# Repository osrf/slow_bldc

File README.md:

# slow_bldc

## parts selection

### microcontrollers
Goal: Fast Cortex-M with FPU (at least for now). HS USB would be nice for tons of datalogging, but not necessarily required.
  * Selection: STM32F303CCT
  * Other parts considered:
    * STM32F723ZET6: a bit spendy but is fast with HS USB, which is neat.
    * STM32F4
      * Access line: F401, F410, F411, F412, F413 only have one ADC
      * Fancier ones have multiple ADC's which would be nicer.
    * Atmel SAM E / V / S

### motor driver
Goal: something completely-integrated with power capacity comfortable for 1A to 2A.
  * Selection: [TI DRV8312](http://www.ti.com/product/DRV8312)

### encoder
Requirements: SPI interface, relatively high resolution
  * Selection: AMS 5048A
    * 14 bit, SPI, 3.3v single-supply, 11 kHz
  * Other parts considered:
    * AMS AS5047D and AS5047P are intended for high-speed BLDC and automatically compensate for encoder latency
      * super cool, but probably not necessary for super low-speed applications
    * Melexis MLX90316
      * 12 bit, SPI
      * 5V supply
      * 1 kHz
    * MPS MA700
      * 3v3 supply, only 7 mA
      * 11 bit
      * 500 kHz
      * can be mounted off-axis and calibrated for donut magnets
    * Allegro A1335
      * 12 bit, SPI
      * can be mounted off-axis
    * AK7451
      * 12 bit
  * Analog output IC's are pretty difference since they output analog sine/cosine, which allows lots of flexibility would would require high-precision simultaneous-sampling ADC to be awesome
    * NXP KMZ60
    * KMT37
    * NVE AAT00x is super low power and tiny since it just provides the sine/cosine half bridges; you need to supply amps and ADC's
    * AS5115 has differential analog sine/cosine outputs

### comms
  * MCU has USB full-speed (12 mbps)
  * Half-duplex RS-485 IC included for chaining these boards together: SN65HVD75

### power supply
  * assumes a regulated 12V supply to provide both the gate-drive and motor bus voltage
  * onboard Recom DC-DC used to generate local 3.3v supply

### current sense
  * TI INA240 used for inline current measurement on flying series current-sense resistors to each phase lead

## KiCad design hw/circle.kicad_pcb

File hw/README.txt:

designed to the no-touch specs at Sierra Circuits:
* 4 layers
* 6mil trace/space = 0.1524mm
* 10mil via hole size = 0.254mm
* 22mil via diameter = 0.5588mm
* 46mm circle outline = 1.811" x 1.811"

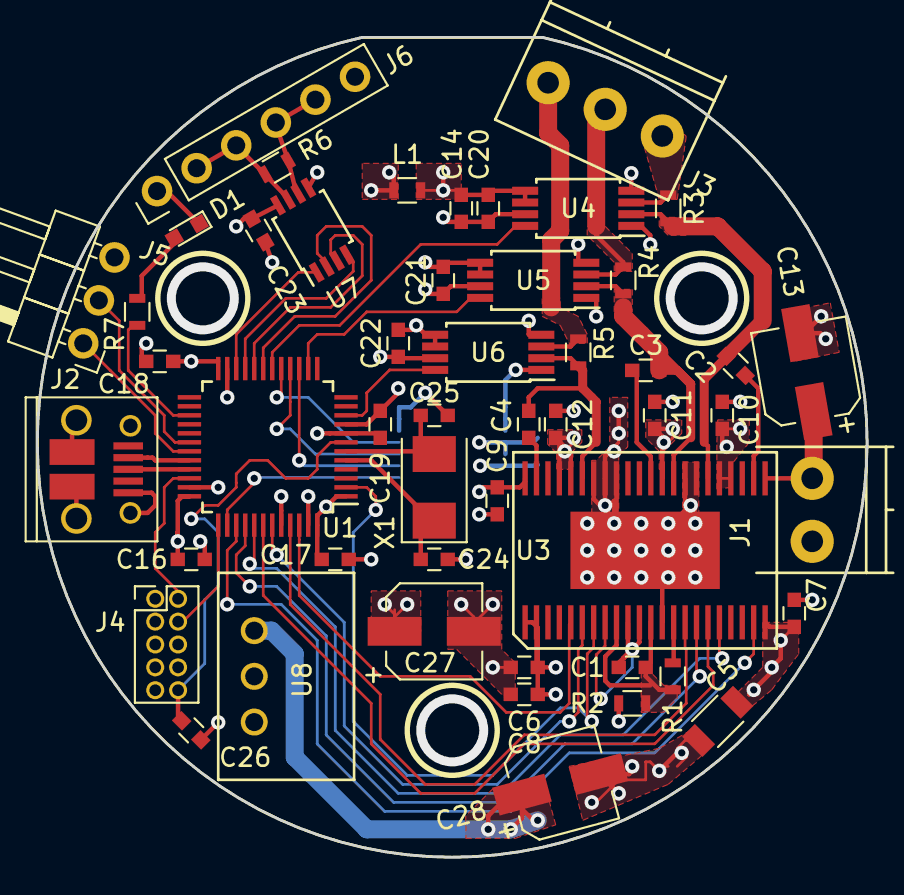
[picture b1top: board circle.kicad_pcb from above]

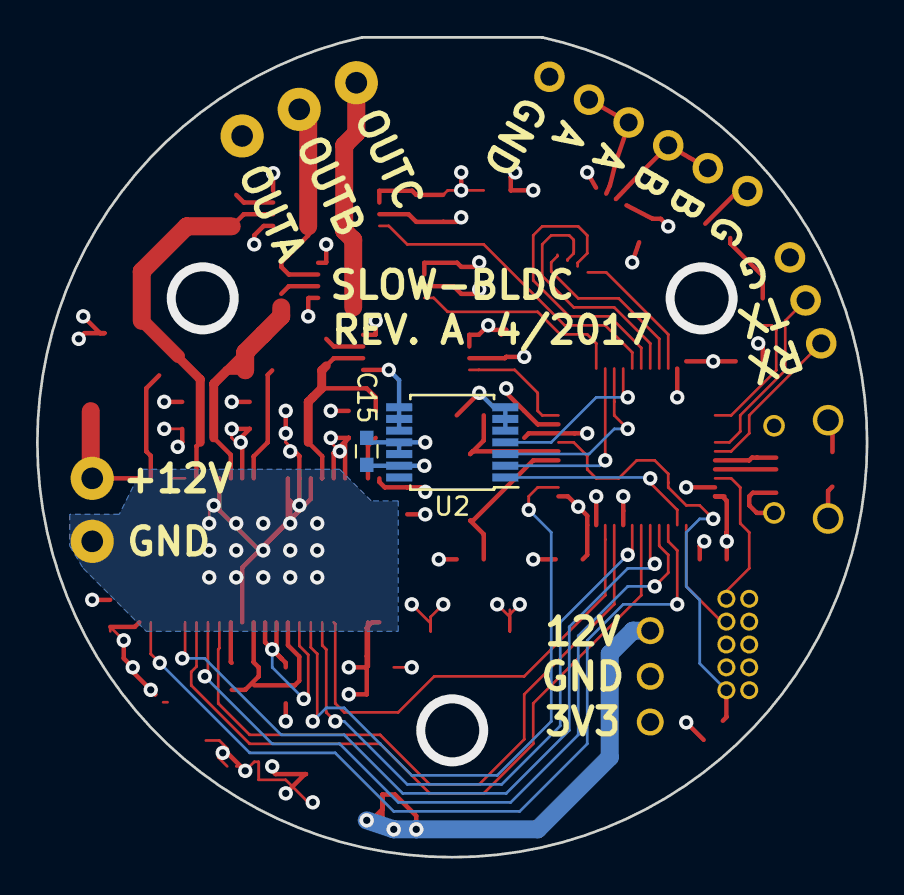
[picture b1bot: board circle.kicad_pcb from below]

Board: 4 copper layers, 46.1 x 45.5 mm, 52 parts (2 on the bottom side), 48 nets.

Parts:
C1, C2, C3, C4, C6, C10, C11, C12, C15, C16, C17, C18, C19, C20, C21, C22, C23, C26: 100n; C_0603
C5: 22u; C_1206
C7, C8, C9, C14: 1u; C_0603
C13, C27, C28: 100u; CP_Elec_5x5.8
C24, C25: 12p; C_0603
D1: LED_Small; LED_0603
J1: CONN_01X02; TerminalBlock_Pheonix_PT-3.5mm_2pol
J2: USB_OTG; USB_Micro-B_10103594-0001LF
J3: CONN_01X03; TerminalBlock_Pheonix_PT-3.5mm_3pol
J4: CONN_02X05; Pin_Header_Straight_2x05_Pitch1.27mm
J5: CONN_01X03; Pin_Header_Angled_1x03_Pitch2.54mm
J6: CONN_01X06; Pin_Header_Straight_1x06_Pitch2.54mm
L1: ferrite; R_0603
R1: 27k0; R_0603
R2: 1; R_0603
R3, R4, R5, R7: 0R05; R_0603
R6: 100; R_0603
U1: STM32F303CCTx; LQFP-48_7x7mm_Pitch0.5mm
U2: AS5048A; TSSOP-14_4.4x5mm_Pitch0.65mm
U3: DRV8312; SOIC-44-POWERPAD
U4, U5, U6: INA240; TSSOP-8_4.4x3mm_Pitch0.65mm
U7: SN65HVD75; TSSOP-8_3x3mm_Pitch0.65mm
U8: R-78xx-0.5
X1: 8 MHz; Crystal_SMD_5032-2pin_5.0x3.2mm

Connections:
+3V3: C15.2, C16.2, C17.2, C18.2, C23.2, C27.1, J4.1, L1.2, U1.1, U1.24, U1.36, U1.48, U2.11, U2.12, U7.8, U8.3
+12V: C5.2, C6.2, C7.2, C8.2, C9.2, C10.2, C11.2, C12.2, C13.1, C28.1, J1.2, U3.1, U3.2, U3.22, U3.23, U3.26, U3.27, U3.32, U3.40, U3.41, U3.44, U8.1
/AGND: C1.1, R1.1, R2.2, U3.9, U3.12
/AMPA: U1.18, U4.8
/AMPB: U1.14, U5.8
/AMPC: U1.10, U6.8
/BSTA: C2.2, U3.24
/BSTB: C3.2, U3.33
/BSTC: C4.2, U3.43
/ENC_CS: U1.38, U2.1
/ENC_MISO: U1.16, U2.3
/ENC_MOSI: U1.17, U2.4
/ENC_SCLK: U1.15, U2.2
/FAULT: U1.41, U3.18
/LED: R7.1, U1.27
/NRST: C26.2, J4.10, U1.7
/OCADJ: R1.2, U3.14
/OSC_IN: C24.2, U1.5, X1.1
/OSC_OUT: C25.2, U1.6, X1.2
/OTW: U1.39, U3.21
/OUTA: J3.1, R3.1, U4.3
/OUTB: J3.2, R4.1, U5.3
/OUTC: J3.3, R5.1, U6.3
/PWMA: U1.42, U3.17
/PWMB: U1.45, U3.15
/PWMC: U1.46, U3.5
/RS485A: J6.4, J6.5, R6.2, U7.6
/RS485B: J6.2, J6.3, R6.1, U7.7
/RS485DE: U1.20, U7.3
/RS485DI: U1.21, U7.4
/RS485RE: U1.19, U7.2
/RS485RO: U1.22, U7.1
/RSTA: U1.40, U3.16
/RSTB: U1.2, U3.7
/RSTC: U1.43, U3.6
/SENSEA: C2.1, R3.2, U3.28, U4.2
/SENSEB: C3.1, R4.2, U3.31, U5.2
/SENSEC: C4.1, R5.2, U3.39, U6.2
/STDIN: J5.1, U1.31
/STDOUT: J5.2, U1.30
/SWCLK: J4.4, U1.37
/SWDIO: J4.2, U1.34
/USBD+: J2.3, U1.33
/USBD-: J2.2, U1.32
/VREG: C1.2, U3.8, U3.10, U3.11
GND: C5.1, C6.1, C7.1, C8.1, C9.1, C10.1, C11.1, C12.1, C13.2, C14.1, C15.1, C16.1, C17.1, C18.1, C19.1, C20.1, C21.1, C22.1, C23.1, C24.1, C25.1, C26.1, C27.2, C28.2, D1.1, J1.1, J2.5, J2.6, J4.3, J4.5, J4.9, J5.3, J6.1, J6.6, R2.1, U1.8, U1.23, U1.35, U1.44, U1.47, U2.5, U2.6, U2.7, U2.8, U2.9, U2.10, U2.13, U3.13, U3.29, U3.30, U3.36, U3.37, U3.38, U3.45, U4.1, U4.4, U4.7, U5.1, U5.4, U5.7, U6.1, U6.4, U6.7, U7.5, U8.2
unnamed: D1.2, R7.2
VAA: C14.2, C19.2, C20.2, C21.2, C22.2, L1.1, U1.9, U4.5, U4.6, U5.5, U5.6, U6.5, U6.6

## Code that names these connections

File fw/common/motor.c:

#include <stdio.h>
#include "motor.h"
#include "pin.h"
#include "st/stm32f303xc.h"

// motor-drive related pins:
#define OTW_GPIO GPIOB
#define OTW_PIN 3

#define FAULT_GPIO GPIOB
#define FAULT_PIN 5

#define RSTA_GPIO GPIOB
#define RSTA_PIN 4

#define RSTB_GPIO GPIOC
#define RSTB_PIN 13

#define RSTC_GPIO GPIOB
#define RSTC_PIN 7

void motor_init()
{
  printf("motor_init()\n");
  pin_set_input(OTW_GPIO, OTW_PIN, false);  // no internal pullup needed
  pin_set_input(FAULT_GPIO, FAULT_PIN, false);
  pin_set_output(RSTA_GPIO, RSTA_PIN, false);
  pin_set_output(RSTB_GPIO, RSTB_PIN, false);
  pin_set_output(RSTC_GPIO, RSTC_PIN, false);
  motor_assert_reset(true);
}

void motor_assert_reset(const bool reset)
{
  pin_set_output_state(RSTA_GPIO, RSTA_PIN, reset ? 0 : 1);
  pin_set_output_state(RSTB_GPIO, RSTB_PIN, reset ? 0 : 1);
  pin_set_output_state(RSTC_GPIO, RSTC_PIN, reset ? 0 : 1);
}

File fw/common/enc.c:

#include <stdio.h>
#include "enc.h"
#include "pin.h"
#include "st/stm32f303xc.h"

#define ENC_GPIO GPIOA
#define ENC_SCLK_PIN 5
#define ENC_MISO_PIN 6
#define ENC_MOSI_PIN 7
#define ENC_CS_PIN 15

void enc_init()
{
  printf("enc_init()\n");
  RCC->APB2ENR |= RCC_APB2ENR_SPI1EN;
  pin_set_alternate_function(ENC_GPIO, ENC_SCLK_PIN, 5);  // PA5 AF5 = SCLK1
  pin_set_alternate_function(ENC_GPIO, ENC_MISO_PIN, 5);  // PA6 AF5 = MISO1
  pin_set_alternate_function(ENC_GPIO, ENC_MOSI_PIN, 5);  // PA7 AF5 = MOSI1
  pin_set_output(ENC_GPIO, ENC_CS_PIN, true);
  pin_set_output_speed(ENC_GPIO, ENC_CS_PIN, 1);  // up to 10 MHz is fine
  pin_set_output_speed(ENC_GPIO, ENC_SCLK_PIN, 1);  // up to 10 MHz is fine
  pin_set_output_speed(ENC_GPIO, ENC_MISO_PIN, 1);  // up to 10 MHz is fine
  pin_set_output_speed(ENC_GPIO, ENC_MOSI_PIN, 1);  // up to 10 MHz is fine
  SPI1->CR1  = SPI_CR1_CPHA |  // clock phase: cpol=0, cpha=1
               SPI_CR1_MSTR |  // master mode
               SPI_CR1_BR_1 |  // baud rate = pclk / 16 = 72/16 = 4.5 MHz
               SPI_CR1_BR_0 ;  // baud rate = pclk / 16 = 72/16 = 4.5 MHz
  SPI1->CR2  = SPI_CR2_DS_3 |
               SPI_CR2_DS_2 |
               SPI_CR2_DS_1 |
               SPI_CR2_DS_0 |  // select 16-bit data size
               SPI_CR2_SSOE ;  // automatically assert SS output as needed
  SPI1->CR1 |= SPI_CR1_SPE  ;  // enable SPI
}

uint16_t enc_poll()
{
  pin_set_output_low(ENC_GPIO, ENC_CS_PIN);
  SPI1->DR;  // make sure we've flushed the RX register
  SPI1->DR = 0xffff;
  while (!(SPI1->SR & SPI_SR_RXNE)) { }  // wait for it...
  pin_set_output_high(ENC_GPIO, ENC_CS_PIN);
  return SPI1->DR & 0x3fff; // returns the result of the previous call
}

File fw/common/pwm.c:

#include <stdio.h>
#include "pin.h"
#include "pwm.h"
#include "st/stm32f303xc.h"

// PB6 = TIM8_CH1 on AF5  = PWMA
// PB8 = TIM8_CH2 on AF10 = PWMB
// PB9 = TIM8_CH3 on AF10 = PWMC

#define PWM_GPIO GPIOB

void pwm_init()
{
  printf("pwm_init()\n");
  // here we shall actually set up the timer peripheral
  RCC->APB2ENR |= RCC_APB2ENR_TIM8EN;  // turn on TIM8 clock
  pin_set_alternate_function(PWM_GPIO, 6,  5);  // PB6 AF5  = TIM8_CH1
  pin_set_alternate_function(PWM_GPIO, 8, 10);  // PB8 AF10 = TIM8_CH2
  pin_set_alternate_function(PWM_GPIO, 9, 10);  // PB9 AF10 = TIM8_CH3
  // inbound clock is 72 MHz / 2 = 36 MHz
  TIM8->ARR = 2047;  // this will give us a 36M/2048 = 17.578 kHz timebase
  TIM8->CCR1 = 1024;  // CH1 PWM level to drive 1/2 bus voltage
  TIM8->CCR2 = 1024;  // CH2 PWM level to drive 1/2 bus voltage
  TIM8->CCR3 = 1024;  // CH3 PWM level to drive 1/2 bus voltage
  TIM8->CCMR1 = TIM_CCMR1_OC1M_1 |  // PWM mode 0 on output compare 1 (OC1)
                TIM_CCMR1_OC1M_2 |  // PWM mode 0 on output compare 1 (OC1)
                TIM_CCMR1_OC1CE  |  // clear output 1 on compare
                TIM_CCMR1_OC2M_1 |  // PWM mode 0 on output compare 2 (OC2)
                TIM_CCMR1_OC2M_2 |  // PWM mode 0 on output compare 2 (OC2)
                TIM_CCMR1_OC2CE  ;  // clear output 2 on compare
  TIM8->CCMR2 = TIM_CCMR2_OC3M_1 |  // PWM mode 0 on output compare 3 (OC3)
                TIM_CCMR2_OC3M_2 |  // PWM mode 0 on output compare 3 (OC3)
                TIM_CCMR2_OC3CE  ;  // clear output 3 on compare
  TIM8->CCER  = TIM_CCER_CC1E    |  // enable compare output 1
                TIM_CCER_CC2E    |  // enable compare output 2
                TIM_CCER_CC3E    ;  // enable compare output 3
  TIM8->CR1   = TIM_CR1_CMS_0    |  // enable center-aligned PWM mode
                TIM_CR1_ARPE     |  // auto-reload preload enable (buffered)
                TIM_CR1_CEN      ;  // enable counter
  TIM8->EGR   = TIM_EGR_UG       ;  // generate update event to load registers
  TIM8->BDTR  = TIM_BDTR_MOE     ;  // master output enable
}

void pwm_set(const uint32_t a, const uint32_t b, const uint32_t c)
{
  TIM8->CCR1 = a;
  TIM8->CCR2 = b;
  TIM8->CCR3 = c;
}

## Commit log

2017-03-29 deep thoughts
2017-04-03 stm32f4 notes
2017-04-05 update mcu selection
2017-04-05 skeleton
2017-04-10 encoder shopping
2017-04-10 more encoder searching
2017-04-10 more ams encoder options
2017-04-10 add encoder ic
2017-04-11 filling in the schematic
2017-04-11 rs485 transceiver
2017-04-12 power module selection
2017-04-13 add r-78 dc/dc supply
2017-04-13 schematic
2017-04-13 rs485 connector
2017-04-13 swd, etc.
2017-04-14 capacitors
2017-04-16 assign mcu pins
2017-04-16 mounting holes
2017-04-17 moving placements a bit to clear mounting holes
2017-04-17 initial placement complete
2017-04-17 power planes
2017-04-17 routing
2017-04-18 rev.A sent to fab
2017-04-18 add part numbers
2017-04-25 clean up fab drawing for hand assembly
2017-04-26 fix led resistor value
2017-04-26 add gitignore file
2017-04-26 firmware skeleton. now it can blink.
2017-04-27 add a few more skeletons
2017-05-01 fix build and get console working
2017-05-01 bringing up board. encoder and motor driver IC seem fine.
2017-05-01 gitignore
2017-05-02 software skeleton and beginning of params and rs485 in firmware
2017-05-05 debug rs485 comms. start on control.
2017-05-05 voltage control skeleton
2017-05-05 voltage mode control loop appears to be working.
2017-05-06 position controller looks OK
2017-05-06 cleanup
2017-10-04 tweak tuning and demo position app
